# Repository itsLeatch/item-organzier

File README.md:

# item-organizer

You have problems to find a good place to store small objects that might be useful in the future? Me too! That's why I was building item-organizer.\
Just scan your screws, cables ... with the mobile app and the grabber will handle all of the other stuff. It handles you an available bin over and remembers its position.\
You want to find it later on? Just open up the app again, use the search function and receive the item bin by the grabber!

# Pictures
## Grabber

## App

## PCB

### Power
To power the PCB you will need 24V for the motors. In addition you have to power the esp32 through out the usb-c port to make the logic work :-)

# Page

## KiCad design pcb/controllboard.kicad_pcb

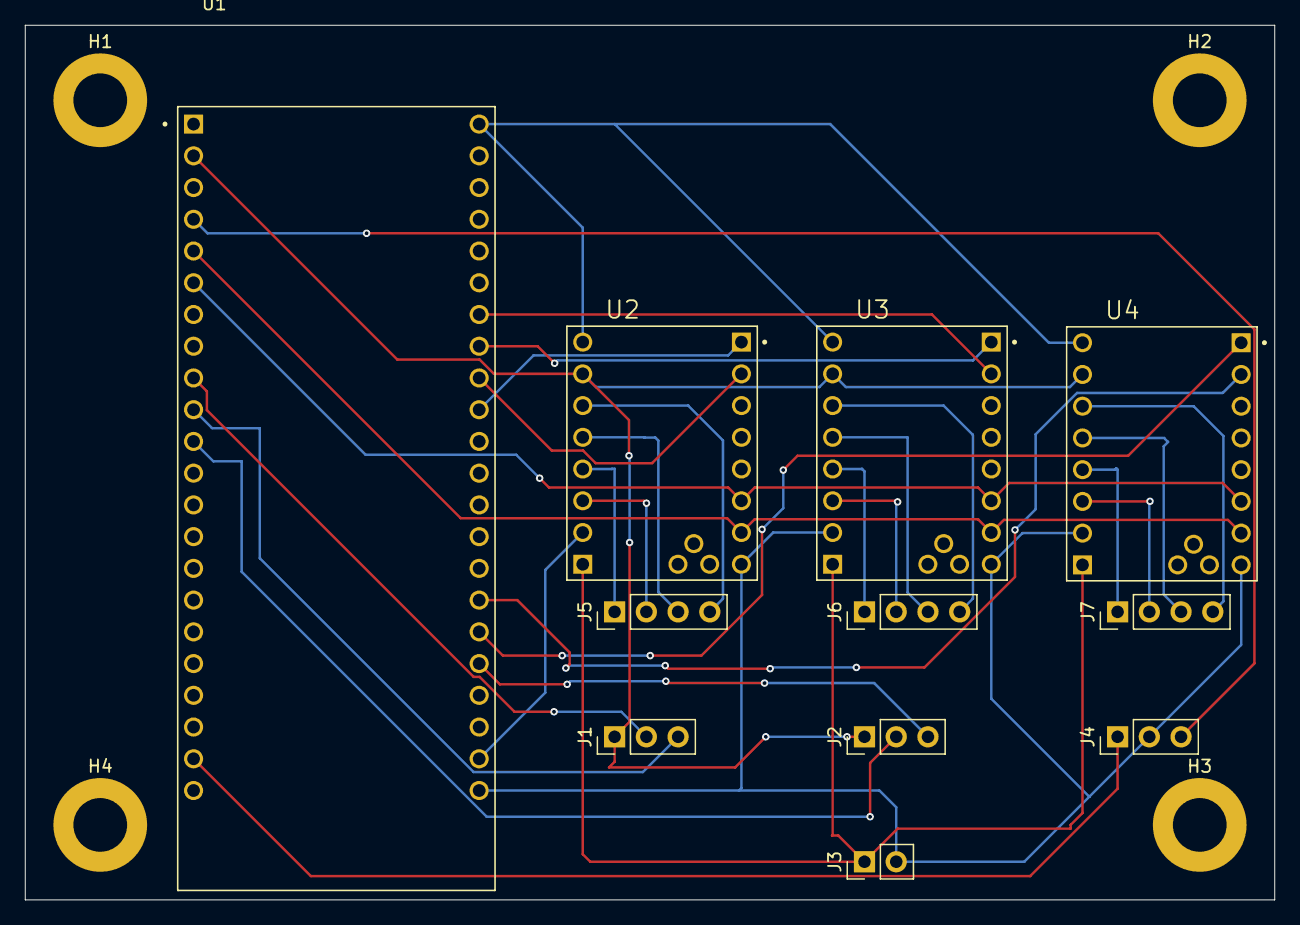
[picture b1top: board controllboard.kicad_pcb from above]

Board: 2 copper layers, 100.0 x 70.0 mm, 15 parts (0 on the bottom side), 29 nets.

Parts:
H1, H2, H3, H4: MountingHole; MountingHole_4.3mm_M4_DIN965_Pad
J1: endstop X; PinHeader_1x03_P2.54mm_Vertical
J2: endstop Y; PinHeader_1x03_P2.54mm_Vertical
J3: 24V Power; PinHeader_1x02_P2.54mm_Vertical
J4: Servo Motor; PinHeader_1x03_P2.54mm_Vertical
J5: X Motor; PinHeader_1x04_P2.54mm_Vertical
J6: Y Motor; PinHeader_1x04_P2.54mm_Vertical
J7: lift Motor; PinHeader_1x04_P2.54mm_Vertical
U1: ESP32-S3-DEVKITC-1-N16R8V; XCVR_ESP32-S3-DEVKITC-1-N16R8V
U2: X Motor; MODULE_TMC2208_SILENTSTEPSTICK
U3: Y Motor; MODULE_TMC2208_SILENTSTEPSTICK
U4: lift Motor; MODULE_TMC2208_SILENTSTEPSTICK

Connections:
3V3: J1.1, J2.1, U1.J1_1 (3V3), U1.J1_2 (3V3), U2.JP2_7 (VIO), U3.JP2_7 (VIO), U4.JP2_7 (VIO)
GND: J3.2, J4.2, U1.J1_22 (GND), U1.J3_1 (GND), U1.J3_21 (GND), U1.J3_22 (GND), U2.JP1_8 (EN), U2.JP2_2 (GND), U2.JP2_8 (GND), U3.JP1_8 (EN), U3.JP2_2 (GND), U3.JP2_8 (GND), U4.JP1_8 (EN), U4.JP2_2 (GND), U4.JP2_8 (GND)
unnamed: J1.2, U1.J1_9 (GPIO16)
unnamed: J1.3, U1.J1_10 (GPIO17)
unnamed: J2.2, U1.J1_11 (GPIO18)
unnamed: J2.3, U1.J3_18 (GPIO21)
unnamed: J3.1, U2.JP2_1 (VM), U3.JP2_1 (VM), U4.JP2_1 (VM)
unnamed: J4.1, U1.J1_21 (5V0)
unnamed: J4.3, U1.J1_4 (GPIO4)
unnamed: J5.1, U2.JP2_4 (OA1)
unnamed: J5.2, U2.JP2_3 (OA2)
unnamed: J5.3, U2.JP2_5 (OB1)
unnamed: J5.4, U2.JP2_6 (OB2)
unnamed: J6.1, U3.JP2_4 (OA1)
unnamed: J6.2, U3.JP2_3 (OA2)
unnamed: J6.3, U3.JP2_5 (OB1)
unnamed: J6.4, U3.JP2_6 (OB2)
unnamed: J7.1, U4.JP2_4 (OA1)
unnamed: J7.2, U4.JP2_3 (OA2)
unnamed: J7.3, U4.JP2_5 (OB1)
unnamed: J7.4, U4.JP2_6 (OB2)
unnamed: U1.J1_5 (GPIO5), U2.JP1_7 (MS1), U3.JP1_7 (MS1), U4.JP1_7 (MS1)
unnamed: U1.J1_6 (GPIO6), U2.JP1_6 (MS2), U3.JP1_6 (MS2), U4.JP1_6 (MS2)
unnamed: U1.J3_10 (GPIO38), U2.JP1_1 (DIR)
unnamed: U1.J3_17 (GPIO47), U4.JP1_1 (DIR)
unnamed: U1.J3_16 (GPIO48), U4.JP1_2 (STEP)
unnamed: U1.J3_9 (MTCK/GPIO39), U2.JP1_2 (STEP)
unnamed: U1.J3_7 (MTDI/GPIO41), U3.JP1_2 (STEP)
unnamed: U1.J3_8 (MTDO/GPIO40), U3.JP1_1 (DIR)
